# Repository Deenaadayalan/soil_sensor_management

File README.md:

View this project on [CADLAB.io](https://cadlab.io/project/29085). 

# soil_sensor_management

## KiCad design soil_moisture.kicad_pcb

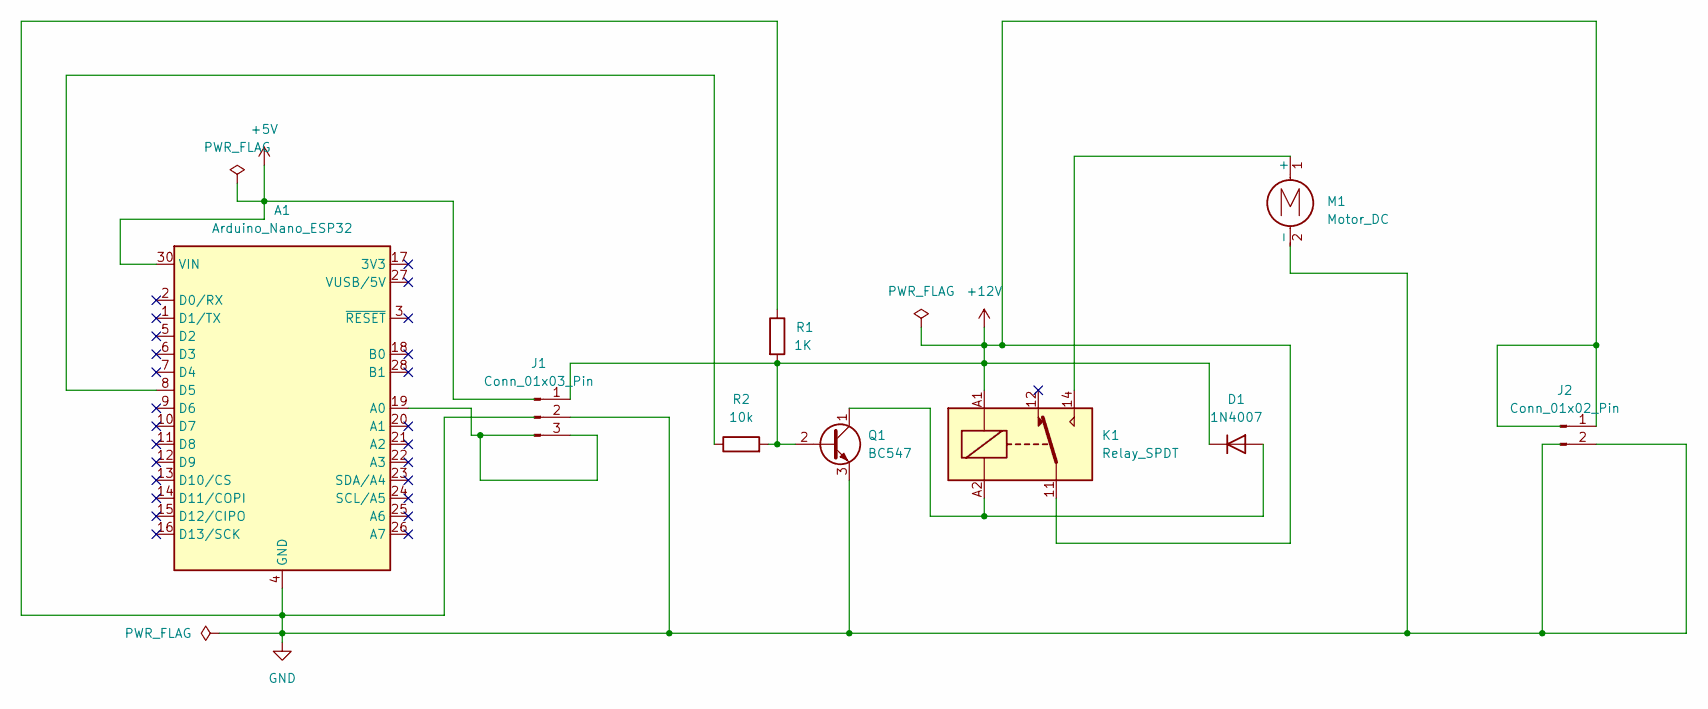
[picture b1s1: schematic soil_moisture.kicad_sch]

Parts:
A1: Arduino_Nano_ESP32; Arduino_Nano
D1: 1N4007; D_DO-41_SOD81_P10.16mm_Horizontal
J1: Conn_01x03_Pin; PinHeader_1x03_P2.54mm_Vertical
J2: Conn_01x02_Pin; PinHeader_1x02_P2.54mm_Vertical
K1: Relay_SPDT; Relay_SPDT_Finder_34.51_Vertical
M1: Motor_DC; PinHeader_1x02_P2.54mm_Vertical
Q1: BC547; TO-92_Inline
R1: 1K; R_Axial_DIN0207_L6.3mm_D2.5mm_P7.62mm_Horizontal
R2: 10k; R_Axial_DIN0207_L6.3mm_D2.5mm_P7.62mm_Horizontal

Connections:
+5V: A1.30 (VIN)
+12V: D1.1 (K), J1.1, J2.1, K1.11, K1.A1, Q1.2 (B), R1.2, R2.2
GND: A1.4 (GND), A1.29 (GND), J1.2, J2.2, M1.2 (-), Q1.3 (E), R1.1
unnamed: A1.19 (A0), J1.3
unnamed: A1.8 (D5), R2.1
unnamed: D1.2 (A), K1.A2, Q1.1 (C)
unnamed: K1.14, M1.1 (+)

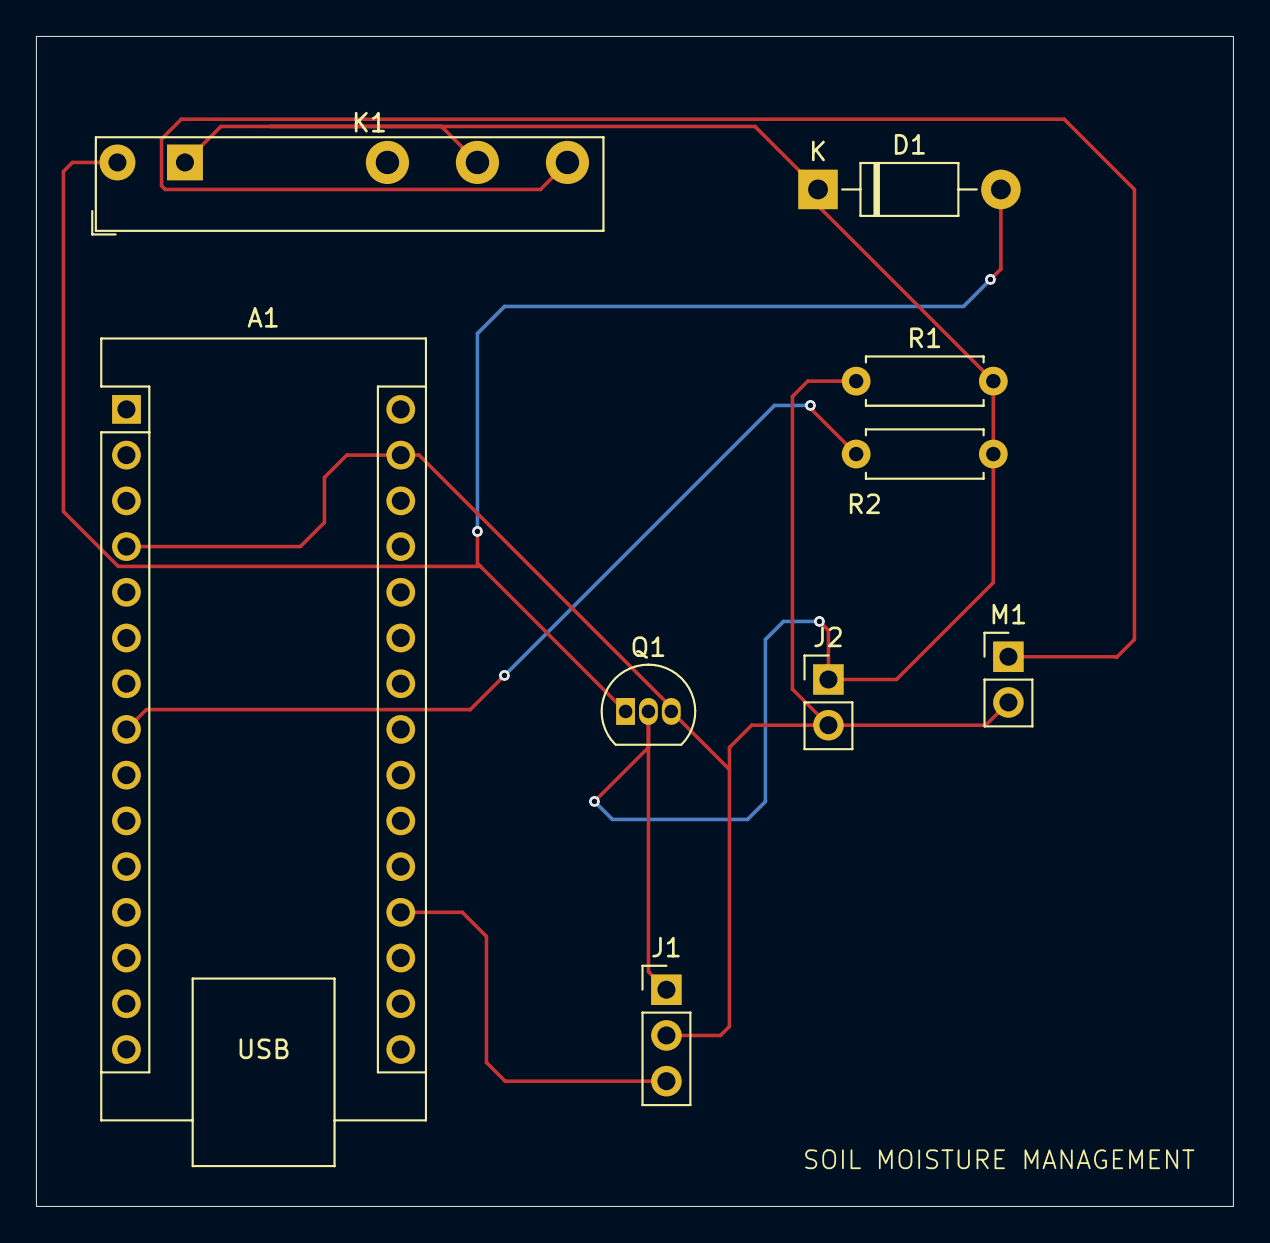
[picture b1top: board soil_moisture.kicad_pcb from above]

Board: 2 copper layers, 66.5 x 65.0 mm, 9 parts (0 on the bottom side), 6 nets.

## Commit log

2025-03-30 KiCad project
2025-03-30 Initial commit with KiCad project and fabrication files
2025-03-30 Backlink to CADLAB.io has been added.
2025-04-07 final cki
